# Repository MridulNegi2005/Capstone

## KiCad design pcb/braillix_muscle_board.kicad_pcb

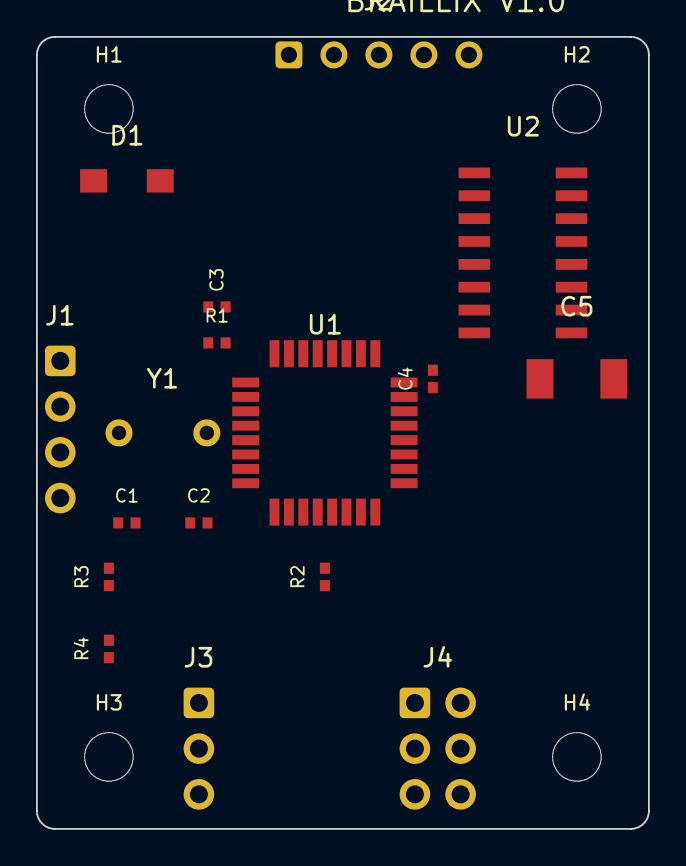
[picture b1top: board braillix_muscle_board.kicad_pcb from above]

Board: 2 copper layers, 34.0 x 44.0 mm, 21 parts (0 on the bottom side), 19 nets, no tracks yet.

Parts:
C1, C2: 22pF; C_0402_1005Metric
C3, C4: 100nF; C_0402_1005Metric
C5: 100uF/10V; CP_Elec_5x5.3
D1: SS14; D_SMA
H1, H2, H3, H4: MountingHole; MountingHole_2.7mm_M2.5
J1: POGO_I2C; PinHeader_1x04_P2.54mm_Vertical
J2: MOTOR_JST; JST_XH_B5B-XH-A_1x05_P2.50mm_Vertical
J3: HALL_SENSOR; PinHeader_1x03_P2.54mm_Vertical
J4: ICSP; PinHeader_2x03_P2.54mm_Vertical
R1, R2: 10K; R_0402_1005Metric
R3, R4: 4K7; R_0402_1005Metric
U1: ATmega328P-AU; TQFP-32_7x7mm_P0.8mm
U2: ULN2003A; SOIC-16_3.9x9.9mm_P1.27mm
Y1: 16MHz; Crystal_HC49-4H_Vertical

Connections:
+5V: C3.1, C4.1, C5.1, D1.1, J1.1, J2.5, J3.1, J4.2, R1.1, R2.1, R3.1, R4.1, U1.4, U1.6, U1.18, U1.20, U2.9
GND: C1.2, C2.2, C3.2, C4.2, C5.2, J1.2, J3.2, J4.6, U1.3, U1.5, U1.21, U2.8
HALL_OUT: J3.3, R2.2, U1.23
IN1: U1.2, U2.1
IN2: U1.9, U2.2
IN3: U1.10, U2.3
IN4: U1.11, U2.4
MISO: J4.1, U1.16
MOSI: J4.4, U1.15
MOTOR_A: J2.1, U2.16
MOTOR_B: J2.2, U2.15
MOTOR_C: J2.3, U2.14
MOTOR_D: J2.4, U2.13
RESET: J4.5, R1.2, U1.29
SCK: J4.3, U1.17
SCL: J1.4, R4.2, U1.28
SDA: J1.3, R3.2, U1.27
XTAL1: C1.1, U1.7, Y1.1
XTAL2: C2.1, U1.8, Y1.2

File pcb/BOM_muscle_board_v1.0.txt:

===============================================================================
BRAILLIX MUSCLE BOARD v1.0 — Bill of Materials (per cell)
Board: 34 x 44mm, 2-layer, 1.6mm FR4, 1oz Cu, HASL lead-free
Generated: 2026-05-16
===============================================================================

Qty | Ref  | Value         | Package            | Description / Notes
----|------|---------------|--------------------|------------------------------------------
 1  | U1   | ATmega328P-AU | TQFP-32 (7x7mm)   | Microchip AVR MCU, I2C slave + motor ctrl
    |      |               |                    | Pre-program Arduino bootloader via ICSP
 1  | U2   | ULN2003A      | SOIC-16 (3.9x9.9)  | TI Darlington array, 500mA/ch, motor driver
 1  | Y1   | 16 MHz        | HC49-4H Vertical   | Crystal oscillator for ATmega328P
 2  | C1,C2| 22 pF         | 0402 (1005 Metric) | C0G/NP0, crystal load capacitors
 2  | C3,C4| 100 nF        | 0402 (1005 Metric) | X7R, VCC + AVCC decoupling caps
 1  | C5   | 100 uF / 10V  | SMD Elec 5x5.3mm   | Aluminium electrolytic, motor bulk bypass
 1  | R1   | 10K ohm       | 0402 (1005 Metric) | RESET pin pull-up to +5V
 1  | R2   | 10K ohm       | 0402 (1005 Metric) | Hall sensor signal pull-up to +5V
 2  | R3,R4| 4.7K ohm      | 0402 (1005 Metric) | I2C pull-ups (SDA, SCL) — enable via jumper
 1  | D1   | SS14          | SMA (DO-214AC)     | 1A 40V Schottky, reverse polarity protection
 1  | J1   | 1x04 header   | 2.54mm vertical    | Pogo pad interface: +5V, GND, SDA, SCL
 1  | J2   | JST XH 5-pin  | B5B-XH-A 2.50mm   | 28BYJ-48 stepper motor connector
 1  | J3   | 1x03 header   | 2.54mm vertical    | Hall sensor: VCC, GND, SIGNAL
 1  | J4   | 2x03 header   | 2.54mm vertical    | AVR ISP (ICSP) programming interface
 4  | H1-4 | M2.5 hole     | 2.7mm NPTH         | Board mounting, matches cell bosses

===============================================================================
TOTAL UNIQUE PARTS:  15 line items
TOTAL COMPONENTS:    19 parts per board (excluding mounting holes)
===============================================================================

SOURCING NOTES:
- ATmega328P-AU: LCSC C14877, Mouser 556-ATMEGA328P-AU (~$2.50)
- ULN2003A SOIC: LCSC C7386, TI ULN2003ADR (~$0.30)
- Crystal 16MHz HC49: LCSC C32346 (~$0.15)
- SS14 Schottky: LCSC C2480 (~$0.05)
- JST XH 5-pin: LCSC C2316 (~$0.10)
- 0402 passives: LCSC generic stock (~$0.01 each)
- 100uF/10V SMD elec: LCSC C131307 (~$0.15)
- Pin headers: cut from 40-pin strip (~$0.05)

ESTIMATED BOM COST: ~$3.50 per board (LCSC/JLCPCB pricing, qty 10+)
PCB FABRICATION: ~$0.40/board (JLCPCB, 5-board MOQ, 2-layer, 1oz)

===============================================================================
I2C ADDRESS CONFIGURATION:
  Solder jumpers on PB0-PB2 set address 0x20-0x27
  Internal pull-ups enabled in firmware (no external resistors needed)
  Default (all open) = 0x27 (all pulled HIGH)
  Short A0 to GND = 0x26, short A0+A1 = 0x24, etc.

I2C PULL-UP CONFIGURATION:
  R3 (SDA) and R4 (SCL) are 4.7K pull-ups to +5V.
  Enable by bridging solder jumper pads near R3/R4.
  Only enable on the LAST cell in the I2C chain.
  All other cells: leave jumper pads open.

MOTOR CONNECTOR PINOUT (J2, JST XH 5-pin):
  Pin 1: Coil A (Blue wire on 28BYJ-48)
  Pin 2: Coil B (Pink wire)
  Pin 3: Coil C (Yellow wire)
  Pin 4: Coil D (Orange wire)
  Pin 5: Common +5V (Red wire)

POGO CONNECTOR PINOUT (J1, 1x04):
  Pin 1: +5V (power chain)
  Pin 2: GND (power chain)
  Pin 3: SDA (I2C data)
  Pin 4: SCL (I2C clock)
===============================================================================

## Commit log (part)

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2026-01-27 Init
2026-01-27 gitignore
2026-01-27 basic braille convertor for a-z, 0-9 and few special chars. LOGIC ONLY
2026-01-27 modified: .gitignore
2026-02-17 Renders
2026-05-02 refreshed designs
2026-05-02 fixed file structures
2026-05-02 temp hardware models
2026-05-02 added hardware renders
2026-05-05 added buttons
2026-05-05 blender scene changes
2026-05-06 Audit redesign v4.0: fix 7 critical failures + add ESP32 pod
    - outer_box v4.0: elec_pocket 9→16mm, shell 50→57/60→68mm, mid-plate+collar,
    wire gutters, pogo recess, magnetic snap (no screws)
    - base_plate v2.2: motor body offset -8mm from shaft, widen to 56mm
    - linkage v3.0: inline feet at Y=0 (fixes Braille scrambling), dot 1/4 gap 2.0mm safe
    - top_plate v3.0: resize 52×60mm, round holes, spring pockets
    - braille_cam2 v2: hub inverts below disc, top clear
2026-05-06 fixed issues with joined mid plate and weird combs and few other changes
2026-05-06 eps32 module
2026-05-10 v4.1
2026-06-02 fix: enlarge cam disc inner_radius 8→12 to prevent linkage binding
    At inner_radius=8, track 0 arc-per-state was 0.87mm — the 2.0mm
    linkage foot straddled 2.3 states simultaneously, causing binding.
    Now at inner_radius=12, worst case is 1.6 states. Cam OD grows
    from 36.4→44.4mm; pocket enlarged 37→46mm (fits 56x50 plate).
    Also:
    - Rename braille_cam2.scad → braille_cam.scad (delete old deprecated v1)
2026-06-03 docs: add solderless breadboard bring-up plan + cross-agent review request
    - docs/BREADBOARD_TEST.md: wiring + test sketch for ESP32 + ULN2003 +
    28BYJ-48 + hall, fully solderless (breadboard + dupont + screw-terminal jack)
    - Flags ESP32 5V-tolerance risk: hall needs 10k+20k divider if it's a 5V module
    - Handoff to Codex + Antigravity to ID hall module + resistors from photos
    and audit wiring before power-on (.ai-sync artifact + handoff updated)
    - Also: shopping list PDF, updated workshop README with Numakers PETG-HS specs
2026-06-03 feat: add complete breadboard wiring guide + test firmware
    - docs/BREADBOARD_STEP_BY_STEP.md: every single wire numbered (12 total),
    pin-by-pin for a CS student with no hardware experience
    - firmware/breadboard_test/breadboard_test.ino: upload-and-run test sketch
    (motor CW/CCW + hall analog reading + continuous monitor)
    - Hall module ID'd as KY-024 (MH-Sensor-Series): power from 3V3, AO→GPIO34,
    no voltage divider needed. Resistors are 4.7k (I2C pull-ups for later).
2026-06-03 firmware: AccelStepper + WiFi web monitor + OTA for breadboard test
    - Replace manual half-step with AccelStepper (HALF4WIRE, IN1/IN3/IN2/IN4)
    for smooth accel/decel and non-blocking motion on ESP32
    - Add WiFi web dashboard (live hall + position, motor control buttons)
    - Add ArduinoOTA so future uploads are wireless (pass "braillix")
    - Correct STEPS_PER_REV 2048 -> 4096 (28BYJ-48 half-step, 64:1 gearbox)
    - Edge-midpoint hall homing; serial mirrors web activity
2026-06-03 cad: v6.0 pre-patent polish + cam double-D bore
    Cam:
    - braille_cam Double-D bore (two opposite flats) + deeper hub (8mm total
    engagement) for the 10mm 28BYJ-48 shaft
    v6.0 polish (full audit in .ai-sync/artifacts/cad_audit_v6_2026-06-04.md):
    - Delete scrapped linkage_comb (stale inner_radius=8; linkages constrained
    at both ends by cam foot + top-plate hole)
